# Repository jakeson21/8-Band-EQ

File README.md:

# 8-Band-EQ
Eight band analog EQ

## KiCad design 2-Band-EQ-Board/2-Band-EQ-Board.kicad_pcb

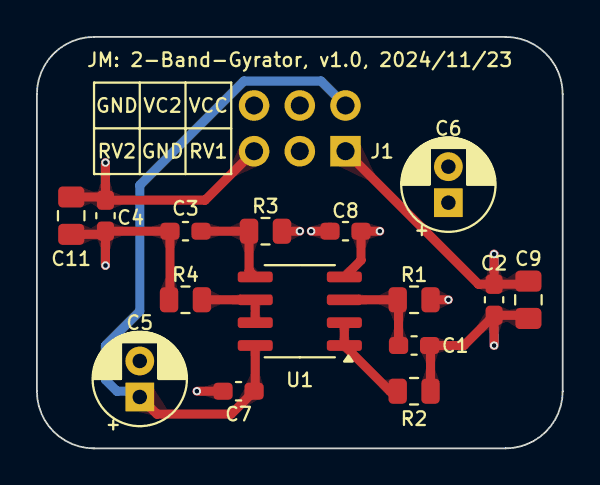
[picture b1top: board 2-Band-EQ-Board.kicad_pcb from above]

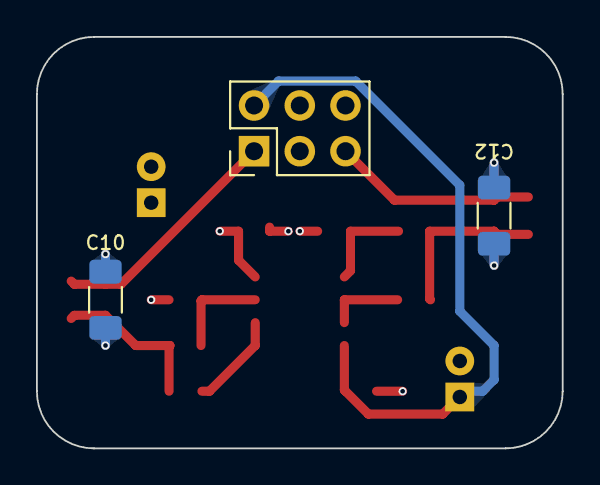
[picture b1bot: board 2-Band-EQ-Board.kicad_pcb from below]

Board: 4 copper layers, 29.2 x 22.9 mm, 18 parts (3 on the bottom side), 11 nets.

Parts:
C1: 33n; C_0603_1608Metric_Pad1.08x0.95mm_HandSolder
C2: 0.68u; C_0603_1608Metric_Pad1.08x0.95mm_HandSolder
C3: 15n; C_0603_1608Metric_Pad1.08x0.95mm_HandSolder
C4: 0.33u; C_0603_1608Metric_Pad1.08x0.95mm_HandSolder
C5, C6: 100u; CP_Radial_D5.0mm_P2.00mm
C7, C8: 0.1u; C_0603_1608Metric_Pad1.08x0.95mm_HandSolder
C9, C11: 1.5u; C_0805_2012Metric_Pad1.18x1.45mm_HandSolder
C10, C12: 3.3u; C_1206_3216Metric_Pad1.33x1.80mm_HandSolder
J1: PHED-DS006G1ABOGA-A006; PinHeader_2x03_P2.54mm_Vertical
R1, R3: 100K; R_0805_2012Metric
R2, R4: 330; R_0805_2012Metric
U1: 296-TL072HIDRCT-ND; SOIC-8_3.9x4.9mm_P1.27mm

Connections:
/RV1: C2.2, C9.2, C10.2, J1.1
/RV2: C4.2, C11.2, C12.2, J1.5
/VCC/2: C5.2, C6.1, C7.1, C8.2, J1.4, R1.1, R3.1
GNDA: C6.2, C8.1, J1.3, J1.6, U1.4 (V-)
unnamed: C1.2, C2.1, C9.1, C10.1, R2.1
unnamed: C3.2, C4.1, C11.1, C12.1, R4.1
unnamed: C1.1, R1.2, U1.3 (+)
unnamed: R2.2, U1.1, U1.2 (-)
unnamed: C3.1, R3.2, U1.5 (+)
unnamed: R4.2, U1.6 (-), U1.7
VCC: C5.1, C7.2, J1.2, U1.8 (V+)

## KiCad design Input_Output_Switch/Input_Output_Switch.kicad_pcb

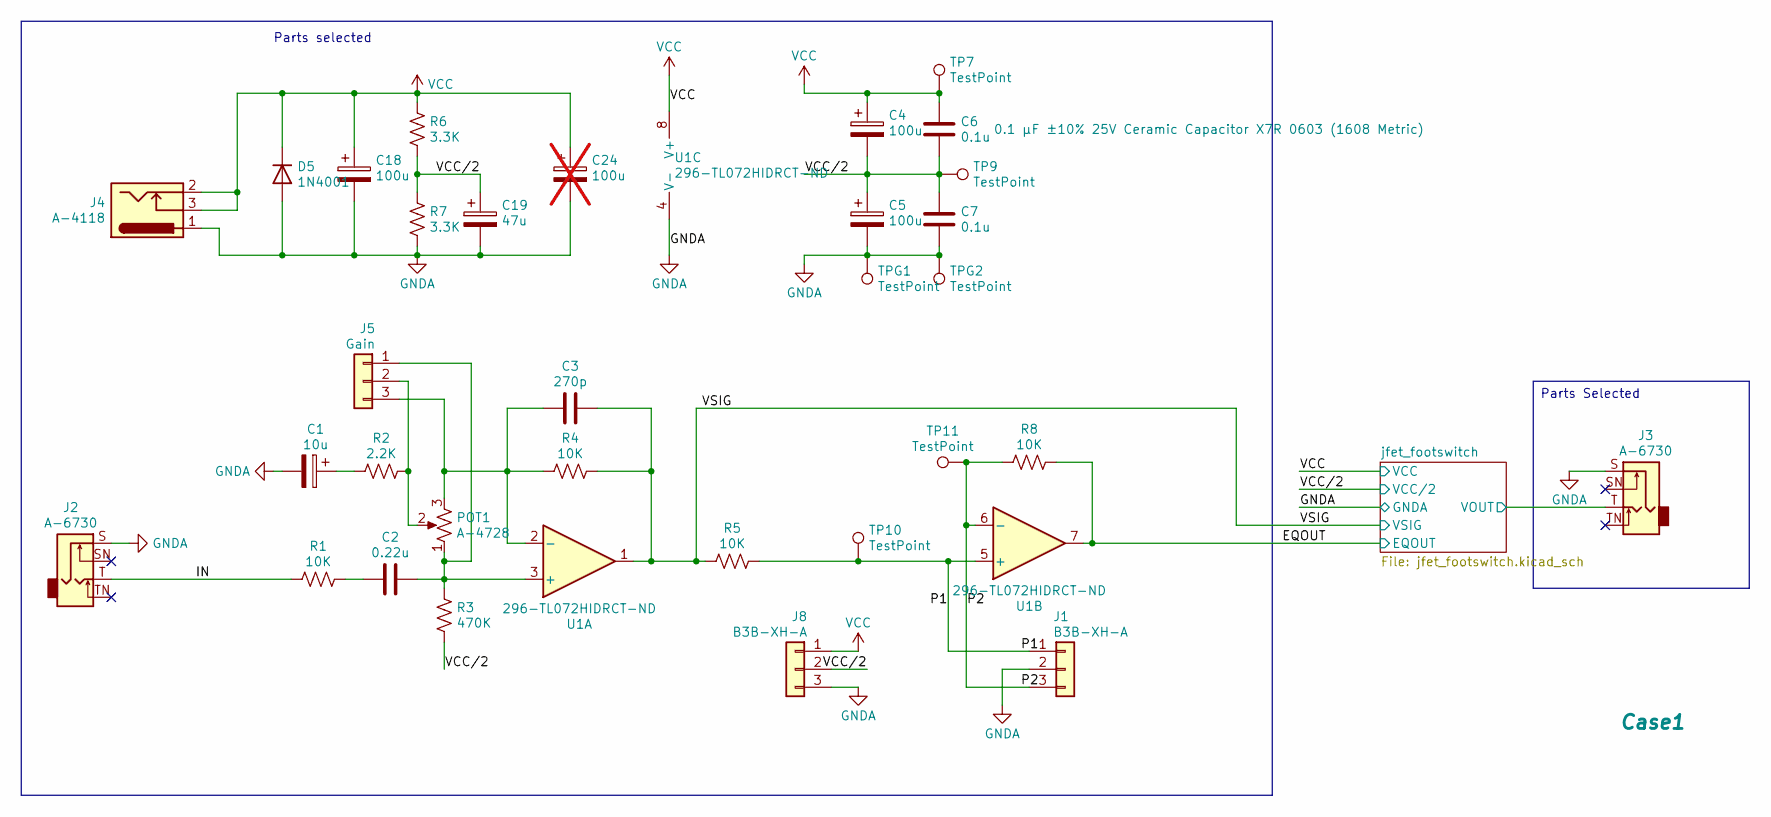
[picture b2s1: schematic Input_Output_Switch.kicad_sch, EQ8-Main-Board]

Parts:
C1: 10u; CP_Elec_4x5.4
C2: 0.22u; C_0603_1608Metric_Pad1.08x0.95mm_HandSolder
C3: 270p; C_0603_1608Metric_Pad1.08x0.95mm_HandSolder
C4, C5, C18: 100u; CP_Radial_D5.0mm_P2.00mm
C6, C7: 0.1u; C_0603_1608Metric_Pad1.08x0.95mm_HandSolder
C19: 47u; CP_Radial_D5.0mm_P2.00mm
C24: 100u; CP_EIA-7343-31_Kemet-D_Pad2.25x2.55mm_HandSolder; not fitted
Case1: Hammond_1444-542
D5: 1N4001; D_DO-41_SOD81_P7.62mm_Horizontal
J1, J8: B3B-XH-A; JST_XH_B3B-XH-A_1x03_P2.50mm_Vertical
J2, J3: A-6730; Jack_6.35mm_Neutrik_NMJ4HFD2_Horizontal
J4: A-4118; BarrelJack_Horizontal
J5: Gain; PinHeader_1x03_P2.54mm_Vertical
POT1: A-4728; Potentiometer_Alpha_RD901F-40-00D_Single_Vertical_CircularH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
R1, R4, R5, R8: 10K; R_0805_2012Metric
R2: 2.2K; R_0805_2012Metric
R3: 470K; R_0805_2012Metric
R6, R7: 3.3K; R_0805_2012Metric
TP7, TP9, TP10, TP11: TestPoint; TestPoint_Pad_1.0x1.0mm
TPG1, TPG2: TestPoint; TestPoint_Pad_1.0x1.0mm
U1: 296-TL072HIDRCT-ND; SOIC-8_3.9x4.9mm_P1.27mm

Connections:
/EQOUT: R8.2, U1.7; also elsewhere on the board
/IN: J2.T, R1.1
/P1: J1.1, R5.2, TP10.1, U1.5 (+)
/P2: J1.3, R8.1, TP11.1, U1.6 (-)
/VSIG: C3.2, R4.2, R5.1, U1.1; also elsewhere on the board
/jfet_footswitch/VOUT: J3.T; also elsewhere on the board
GNDA: C1.2, C5.2, C7.1, C18.2, C19.2, C24.2, D5.2 (A), J1.2, J2.S, J3.S, J4.1, J8.3, R7.2, TPG1.1, TPG2.1, U1.4 (V-); also elsewhere on the board
unnamed: C1.1, R2.2
unnamed: C2.1, R1.2
unnamed: C2.2, J5.1, POT1.1, R3.2, U1.3 (+)
unnamed: J5.2, POT1.2, R2.1
unnamed: C3.1, J5.3, POT1.3, R4.1, U1.2 (-)
VCC: C4.1, C6.2, C18.1, C24.1, D5.1 (K), J4.2, J4.3, J8.1, R6.1, TP7.1, U1.8 (V+); also elsewhere on the board
VCC/2: C4.2, C5.1, C6.1, C7.2, C19.1, J8.2, R3.1, R6.2, R7.1, TP9.1; also elsewhere on the board

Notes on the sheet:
Parts selected
Parts Selected

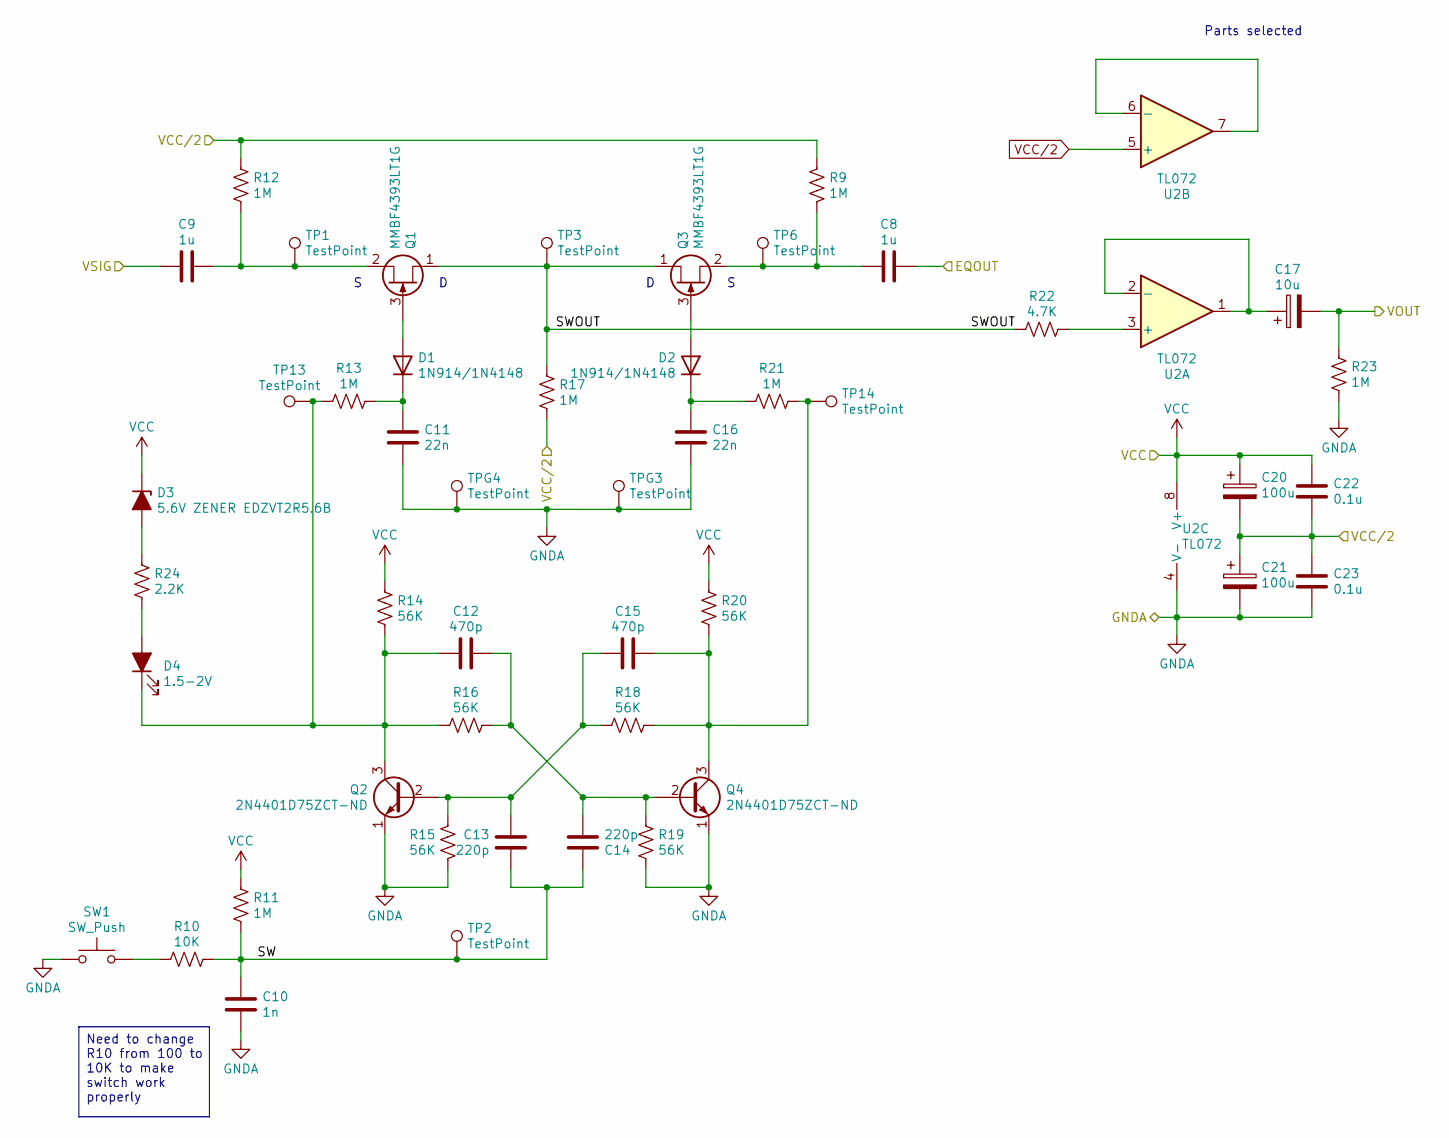
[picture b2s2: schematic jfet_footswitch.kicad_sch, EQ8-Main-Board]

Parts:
C8, C9: 1u; C_0603_1608Metric_Pad1.08x0.95mm_HandSolder
C10: 1n; C_0603_1608Metric_Pad1.08x0.95mm_HandSolder
C11, C16: 22n; C_0603_1608Metric_Pad1.08x0.95mm_HandSolder
C12, C15: 470p; C_0603_1608Metric_Pad1.08x0.95mm_HandSolder
C13, C14: 220p; C_0603_1608Metric_Pad1.08x0.95mm_HandSolder
C17: 10u; CP_Elec_4x5.4
C20, C21: 100u; CP_Radial_D5.0mm_P2.00mm
C22, C23: 0.1u; C_0603_1608Metric_Pad1.08x0.95mm_HandSolder
D1, D2: 1N914/1N4148; D_DO-35_SOD27_P2.54mm_Vertical_AnodeUp
D3: 5.6V ZENER EDZVT2R5.6B; D_SOD-523
D4: 1.5-2V; LED_D3.0mm_Clear
Q1, Q3: MMBF4393LT1G; SOT-23-3
Q2, Q4: 2N4401D75ZCT-ND; TO-92_Inline_Wide
R9, R11, R12, R13, R17, R21, R23: 1M; R_0805_2012Metric
R10: 10K; R_0805_2012Metric
R14, R15, R16, R18, R19, R20: 56K; R_0805_2012Metric
R22: 4.7K; R_0805_2012Metric
R24: 2.2K; R_0805_2012Metric
SW1: SW_Push; Molex_KK-254_AE-6410-02A_1x02_P2.54mm_Vertical
TP1, TP2, TP3, TP6, TP13, TP14: TestPoint; TestPoint_Pad_1.0x1.0mm
TPG3, TPG4: TestPoint; TestPoint_Pad_1.0x1.0mm
U2: TL072; SOIC-8_3.9x4.9mm_P1.27mm

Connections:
/EQOUT: C8.2; also elsewhere on the board
/VSIG: C9.1; also elsewhere on the board
/jfet_footswitch/SW: C10.2, C13.1, C14.2, R10.2, R11.1, TP2.1
/jfet_footswitch/SWOUT: Q1.1 (D), Q3.1 (D), R17.2, R22.2, TP3.1
/jfet_footswitch/VOUT: C17.2, R23.2; also elsewhere on the board
GNDA: C10.1, C11.1, C16.1, C21.2, C23.1, Q2.1 (E), Q4.1 (E), R15.1, R19.1, R23.1, SW1.1, TPG3.1, TPG4.1, U2.4 (V-); also elsewhere on the board
unnamed: D1.2 (A), Q1.3 (G)
unnamed: C11.2, D1.1 (K), R13.2
unnamed: D2.2 (A), Q3.3 (G)
unnamed: C16.2, D2.1 (K), R21.2
unnamed: D3.2 (A), R24.2
unnamed: D4.2 (A), R24.1
unnamed: C12.1, D4.1 (K), Q2.3 (C), R13.1, R14.1, R16.2, TP13.1
unnamed: C9.2, Q1.2 (S), R12.2, TP1.1
unnamed: C13.2, C15.2, Q2.2 (B), R15.2, R18.2
unnamed: C8.1, Q3.2 (S), R9.2, TP6.1
unnamed: C12.2, C14.1, Q4.2 (B), R16.1, R19.2
unnamed: C15.1, Q4.3 (C), R18.1, R20.1, R21.1, TP14.1
unnamed: R10.1, SW1.2
unnamed: R22.1, U2.3 (+)
unnamed: C17.1, U2.1, U2.2 (-)
unnamed: U2.6 (-), U2.7
VCC: C20.1, C22.2, D3.1 (K), R11.2, R14.2, R20.2, U2.8 (V+); also elsewhere on the board
VCC/2: C20.2, C21.1, C22.1, C23.2, R9.1, R12.1, R17.1, U2.5 (+); also elsewhere on the board

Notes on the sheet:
Parts selected
Need to change R10 from 100 to 10K to make switch work properly

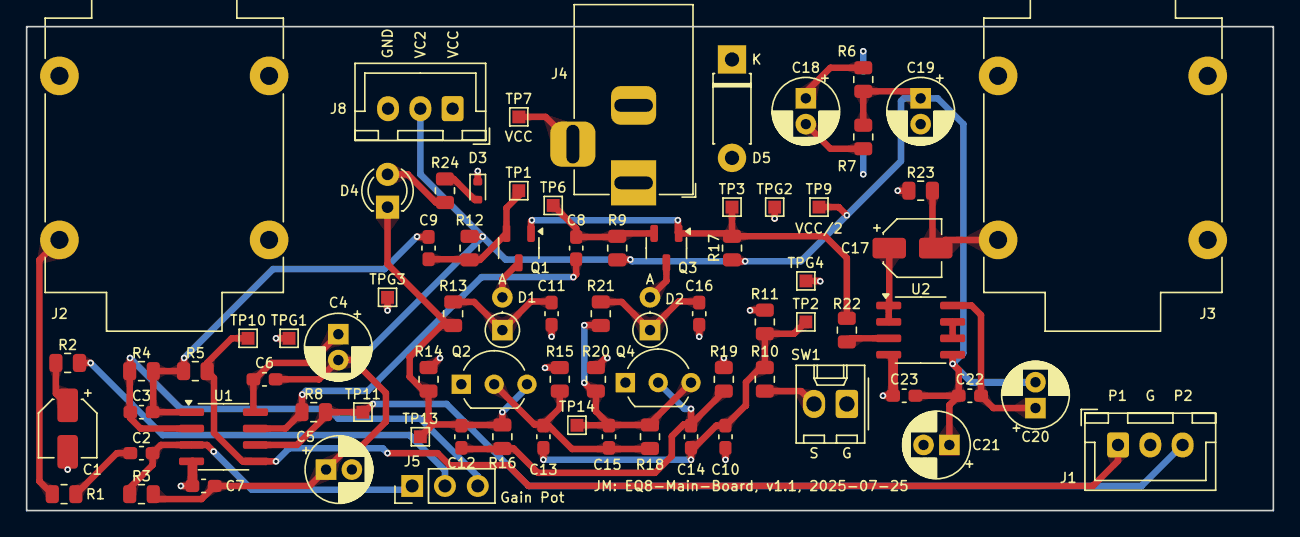
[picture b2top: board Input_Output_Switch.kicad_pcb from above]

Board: 4 copper layers, 96.5 x 37.5 mm, 81 parts (1 on the bottom side), 32 nets.

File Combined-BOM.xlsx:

Reference | Value | Datasheet | Footprint | Qty | DNP
C1,C17 | 10u | https://www.digikey.com/en/products/detail/w%C3%BCrth-elektr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 | Capacitor_SMD:CP_Elec_4x5.4 | 2
C2 | 0.22u | https://www.digikey.com/en/products/detail/murata-electronic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 | Capacitor_SMD:C_0603_1608Metric_Pad1.08x0.95mm_HandSolder | 1
C3 | 270p | https://www.digikey.com/en/products/detail/yageo/CC0603KRX7R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 | Capacitor_SMD:C_0603_1608Metric_Pad1.08x0.95mm_HandSolder | 1
C4,C5,C18,C20,C21 | 100u | https://www.digikey.com/en/products/detail/kemet/ESK107M016A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 | Capacitor_THT:CP_Radial_D5.0mm_P2.00mm | 5
C6,C7,C22,C23 | 0.1u | https://www.digikey.com/en/products/detail/yageo/CC0603KRX7R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 | Capacitor_SMD:C_0603_1608Metric_Pad1.08x0.95mm_HandSolder | 4
C8,C9 | 1u | https://www.digikey.com/en/products/detail/kemet/C0603C105K4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 | Capacitor_SMD:C_0603_1608Metric_Pad1.08x0.95mm_HandSolder | 2
C10 | 1n | https://www.digikey.com/en/products/detail/kemet/C0603C102K4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 | Capacitor_SMD:C_0805_2012Metric | 1
C11,C16 | 22n | https://www.digikey.com/en/products/detail/kemet/C0603C223K4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 | Capacitor_SMD:C_0805_2012Metric | 2
C12,C15 | 470p | https://www.digikey.com/en/products/detail/kemet/C0603C471K3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 | Capacitor_SMD:C_0805_2012Metric | 2
C13,C14 | 220p | https://www.digikey.com/en/products/detail/kemet/C0603C221K3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 | Capacitor_SMD:C_0805_2012Metric | 2
C19 | 47u | https://www.digikey.com/en/products/detail/w%C3%BCrth-elektr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 | Capacitor_THT:CP_Radial_D5.0mm_P2.00mm | 1
C24 | 100u | https://www.digikey.com/en/products/detail/kemet/T491D107K01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 | Capacitor_Tantalum_SMD:CP_EIA-7343-31_Kemet-D_Pad2.25x2.55mm_HandSolder | 1 | DNP
D1,D2 | 1N914 | http://www.vishay.com/docs/85622/1n914.pdf | Diode_THT:D_DO-35_SOD27_P2.54mm_Vertical_AnodeUp | 2
D3 | 5.6V ZENER EDZVT2R5.6B | https://www.rohm.com/datasheet?p=EDZV5.6B&dist=Digi-key&medi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 | Diode_SMD:D_SOD-523 | 1
D4 | 1.5-2V | ~ | LED_THT:LED_D3.0mm_Clear | 1
D5 | 1N4001 | http://www.vishay.com/docs/88503/1n4001.pdf | Diode_THT:D_DO-41_SOD81_P7.62mm_Horizontal | 1
J1,J8 | B3B-XH-A | https://www.digikey.com/en/products/detail/jst-sales-america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 | Connector_JST:JST_XH_B3B-XH-A_1x03_P2.50mm_Vertical | 2
J2,J3 | A-6730 | https://www.taydaelectronics.com/datasheets/files/A-6728.pdf | Project_Library:Jack_6.35mm_Neutrik_NMJ4HFD2_Horizontal | 2
J4 | A-4118 | http://www.taydaelectronics.com/datasheets/files/A-4118.pdf | Connector_BarrelJack:BarrelJack_Horizontal | 1
J5 | Gain | ~ | Connector_PinHeader_2.54mm:PinHeader_1x03_P2.54mm_Vertical | 1
POT1 | A-4728 | https://www.taydaelectronics.com/potentiometer-variable-resi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 | Project_Library:Potentiometer_Alpha_RD901F-40-00D_Single_Vertical_CircularHoles | 1
Q1,Q3 | MMBF4393LT1G | https://www.digikey.com/en/products/detail/onsemi/MMBF4393LT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 | Package_TO_SOT_SMD:SOT-23-3 | 2
Q2,Q4 | 2N4401D75ZCT-ND | https://www.digikey.com/en/products/detail/onsemi/2n4401tar/458821 | Package_TO_SOT_THT:TO-92_Inline_Wide | 2
R1,R4,R5,R8 | 10K | ~ | Resistor_SMD:R_0805_2012Metric | 4
R2,R24 | 2.2K | ~ | Resistor_SMD:R_0805_2012Metric | 2
R3 | 470K | ~ | Resistor_SMD:R_0805_2012Metric | 1
R6,R7 | 3.3K | ~ | Resistor_SMD:R_0805_2012Metric | 2
R9,R11,R12,R13,R17,R21,R23 | 1M | ~ | Resistor_SMD:R_0805_2012Metric | 7
R10 | 100 | ~ | Resistor_SMD:R_0805_2012Metric | 1
R14,R15,R16,R18,R19,R20 | 56K | ~ | Resistor_SMD:R_0805_2012Metric | 6
R22 | 4.7K | ~ | Resistor_SMD:R_0805_2012Metric | 1
SW1 | SW_Push | ~ | Connector_Molex:Molex_KK-254_AE-6410-02A_1x02_P2.54mm_Vertical | 1
U1,U2 | TL072 | http://www.ti.com/lit/ds/symlink/tl071.pdf | Package_SO:SOIC-8_3.9x4.9mm_P1.27mm | 2

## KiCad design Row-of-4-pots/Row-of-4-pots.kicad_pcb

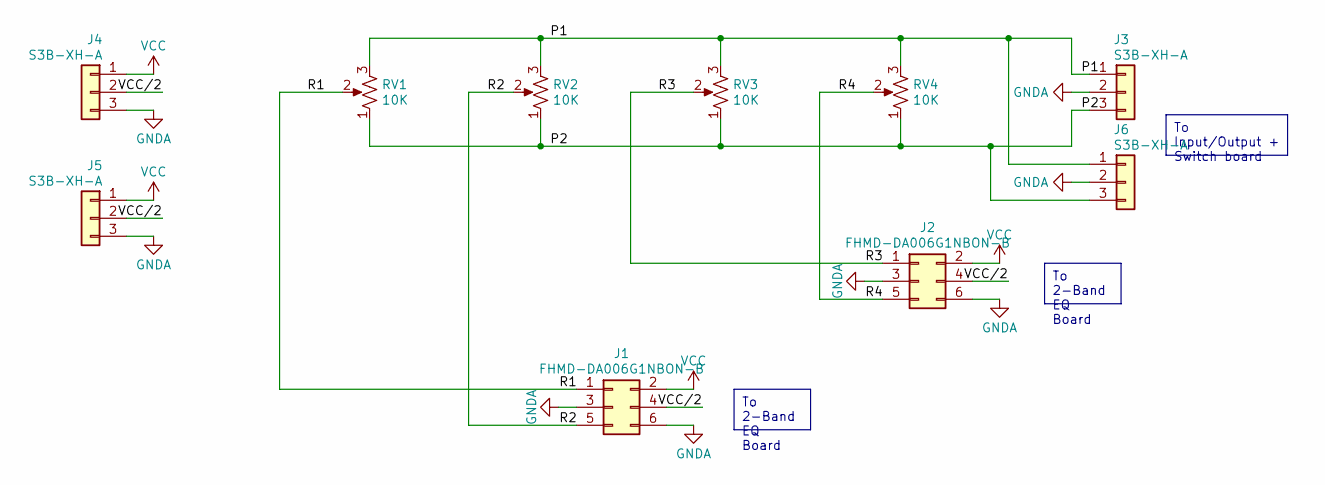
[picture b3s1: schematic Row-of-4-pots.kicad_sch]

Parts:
J1, J2: FHMD-DA006G1NBON-B; PinSocket_2x03_P2.54mm_Vertical
J3, J4, J5, J6: S3B-XH-A; JST_XH_S3B-XH-A_1x03_P2.50mm_Horizontal
RV1, RV2, RV3, RV4: 10K; Potentiometer_Alpha_RD901F-40-00D_Single_Vertical_CircularH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

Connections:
/P1: J3.1, J6.1, RV1.3, RV2.3, RV3.3, RV4.3
/P2: J3.3, J6.3, RV1.1, RV2.1, RV3.1, RV4.1
/R1: J1.1, RV1.2
/R2: J1.5, RV2.2
/R3: J2.1, RV3.2
/R4: J2.5, RV4.2
/VCC/2: J1.4, J2.4, J4.2, J5.2
GNDA: J1.3, J1.6, J2.3, J2.6, J3.2, J4.3, J5.3, J6.2
VCC: J1.2, J2.2, J4.1, J5.1

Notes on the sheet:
To 2-Band EQ Board
To Input/Output + Switch board

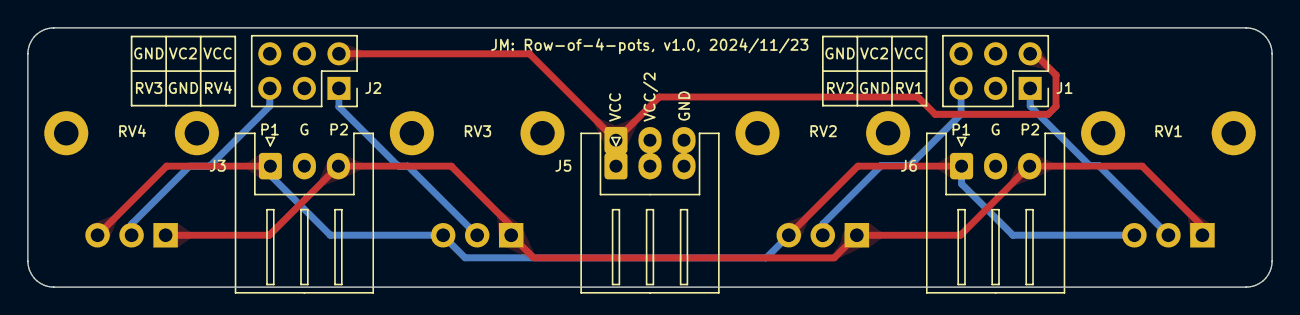
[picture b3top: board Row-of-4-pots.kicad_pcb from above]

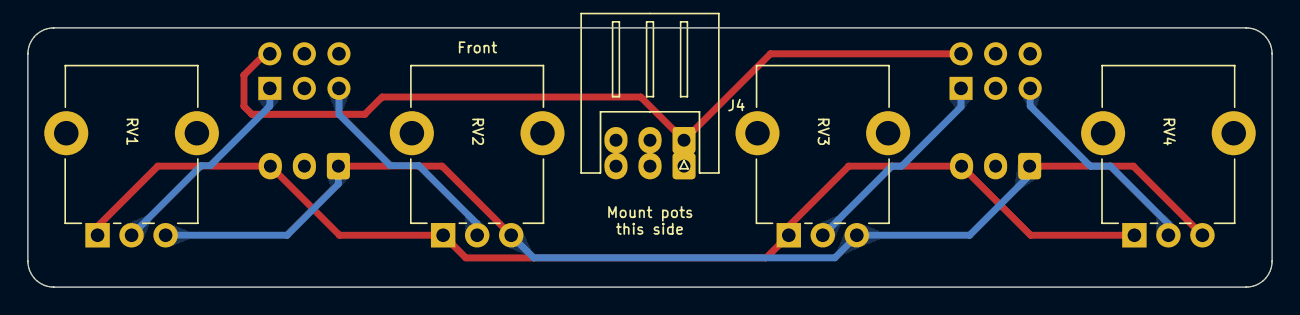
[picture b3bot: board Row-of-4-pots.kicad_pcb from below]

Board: 4 copper layers, 91.4 x 19.0 mm, 10 parts (5 on the bottom side), 9 nets.

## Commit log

2024-11-23 current state of design
2024-11-23 Master merge into main (#1)
    * Initial commit
    * current state of design
2024-11-24 Final version 1.0 ordered
2025-08-23 Fix bypass resistor, add missing Vcc. Move to Kicad-9
